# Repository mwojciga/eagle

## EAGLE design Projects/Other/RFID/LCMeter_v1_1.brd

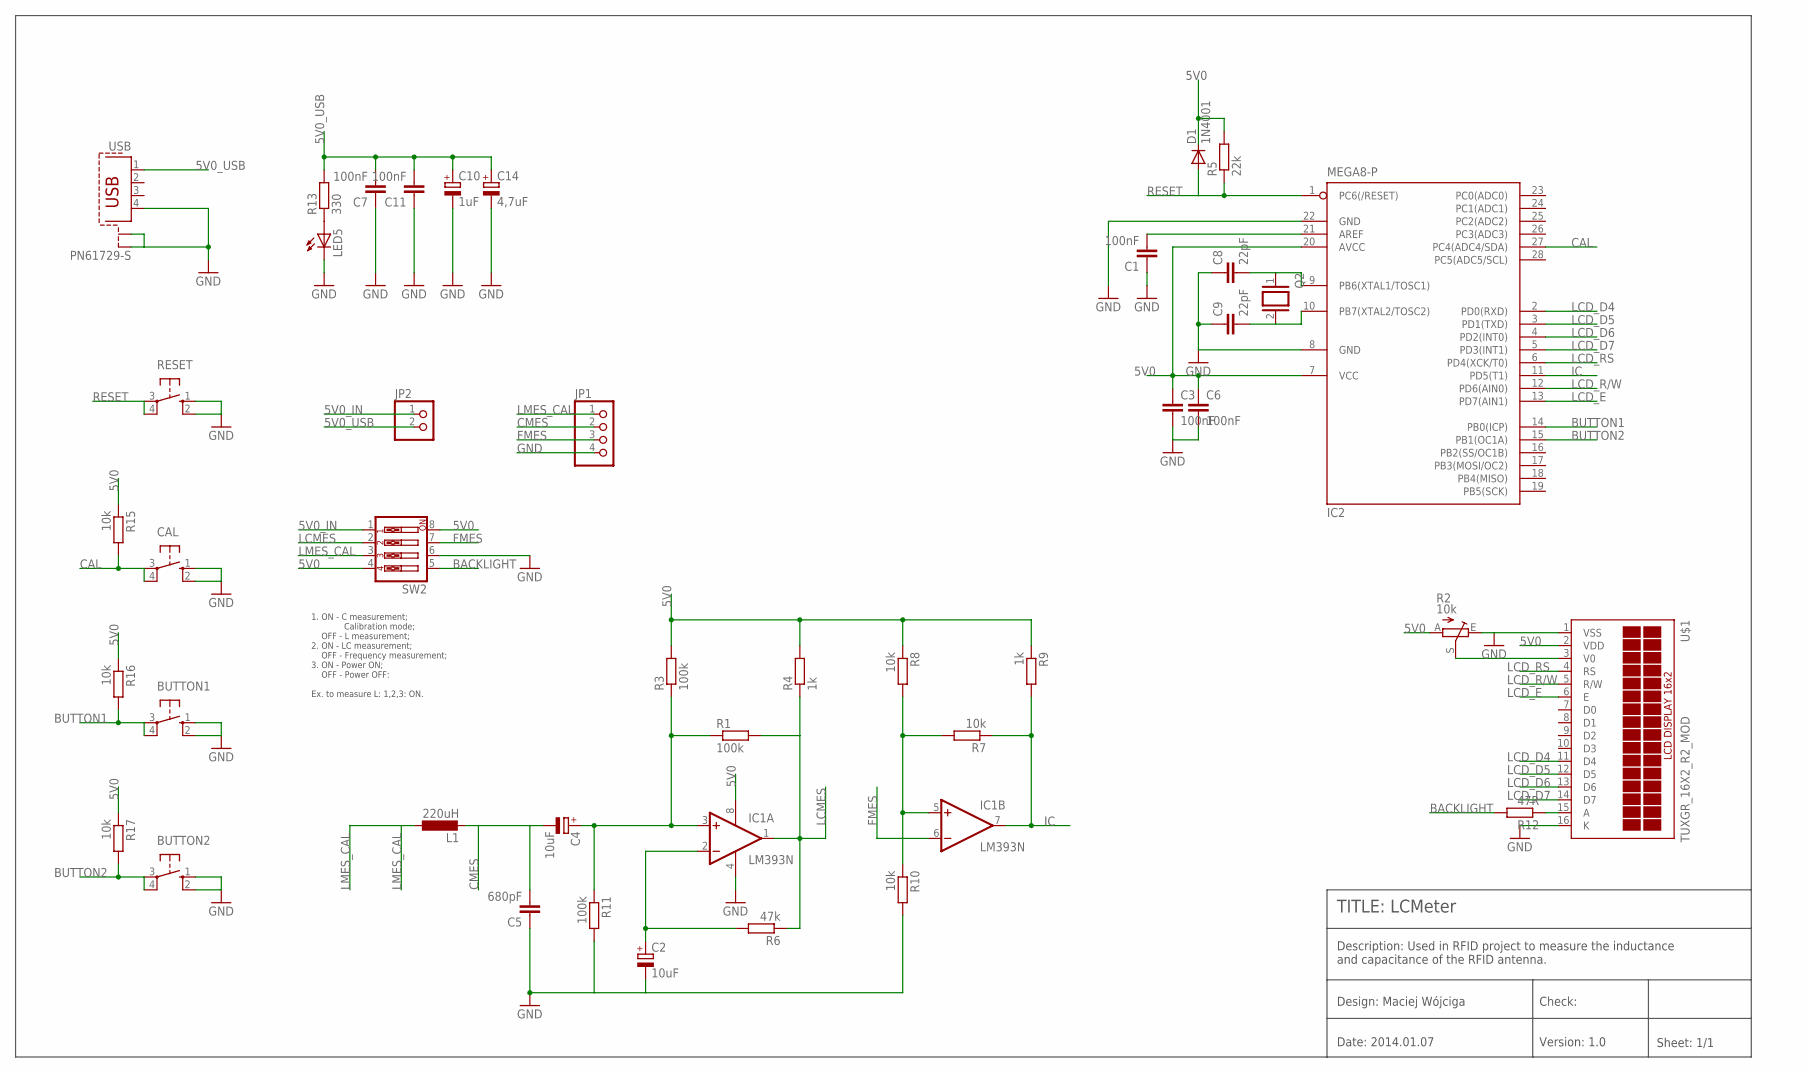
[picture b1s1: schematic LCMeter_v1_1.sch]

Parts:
BUTTON1, BUTTON2: 10-XX; B3F-10XX
C1, C3, C6, C7, C11: 100nF; C025-025X050
C2, C4: 10uF; E2,5-6E
C5: 680pF; C025-025X050
C8, C9: 22pF; C025-025X050
C10: 1uF; E2,5-5
C14: 4,7uF; E2,5-5
CAL: 10-XX; B3F-10XX
D1: 1N4001; DO41-10
IC1: LM393N; DIL08
IC2: MEGA8-P; DIL28-3
JP1: PINHD-1X4; 1X04
JP2: PINHD-1X2/90; 1X02/90
L1: 220uH; 6000-XXXX-RC
LED5: LED3MM
Q2: XTAL/S; QS
R1, R3, R11: 100k; 0207/10
R2: 10k; RJ9W
R4, R9: 1k; 0207/10
R5: 22k; 0207/10
R6: 47k; 0207/10
R7, R8, R10, R15, R16, R17: 10k; 0207/10
R12: 47R; 0207/10
R13: 330; 0207/10
RESET: 10-XX; B3F-10XX
SW2: SW_DIP-4; EDG-04
U$1: TUXGR_16X2_R2_MOD
USB: PN61729-S

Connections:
5V0: C3.1, C6.1, D1.C, IC1.8 (V+), IC2.7 (VCC), IC2.20 (AVCC), R2.A, R3.2, R4.2, R5.2, R8.1, R9.1, R15.1, R16.1, R17.1, SW2.4, SW2.8, U$1.2 (VDD)
5V0_IN: JP2.1, SW2.1
5V0_USB: C7.2, C10.+, C11.2, C14.+, JP2.2, R13.2, USB.1
BACKLIGHT: R12.2, SW2.5
BUTTON1: BUTTON1.3, BUTTON1.4 (P1), IC2.14 (PB0(ICP)), R16.2
BUTTON2: BUTTON2.3, BUTTON2.4 (P1), IC2.15 (PB1(OC1A)), R17.2
CAL: CAL.3, CAL.4 (P1), IC2.27 (PC4(ADC4/SDA)), R15.2
CMES: C4.-, C5.2, JP1.2, L1.2
FMES: IC1.6 (-IN), JP1.3, SW2.7
GND: BUTTON1.1 (S), BUTTON1.2 (S1), BUTTON2.1 (S), BUTTON2.2 (S1), C1.1, C2.-, C3.2, C5.1, C6.2, C7.1, C8.1, C9.1, C10.-, C11.1, C14.-, CAL.1 (S), CAL.2 (S1), IC1.4 (V-), IC2.8 (GND), IC2.22 (GND), JP1.4, LED5.K (C), R2.E, R10.2, R11.2, RESET.1 (S), RESET.2 (S1), SW2.6, U$1.1 (VSS), U$1.16 (K), USB.4, USB.S1, USB.S2
IC: IC1.7 (OUT), IC2.11 (PD5(T1)), R7.1, R9.2
LCD_D4: IC2.2 (PD0(RXD)), U$1.11 (D4)
LCD_D5: IC2.3 (PD1(TXD)), U$1.12 (D5)
LCD_D6: IC2.4 (PD2(INT0)), U$1.13 (D6)
LCD_D7: IC2.5 (PD3(INT1)), U$1.14 (D7)
LCD_E: IC2.13 (PD7(AIN1)), U$1.6 (E)
LCD_R/W: IC2.12 (PD6(AIN0)), U$1.5 (R/W)
LCD_RS: IC2.6 (PD4(XCK/T0)), U$1.4 (RS)
LCMES: IC1.1 (OUT), R1.2, R4.1, R6.1, SW2.2
LMES_CAL: JP1.1, L1.1, SW2.3
unnamed: C1.2, IC2.21 (AREF)
unnamed: C2.+, IC1.2 (-IN), R6.2
unnamed: R2.S, U$1.3 (V0)
unnamed: C4.+, IC1.3 (+IN), R1.1, R3.1, R11.1
unnamed: LED5.A, R13.1
unnamed: IC1.5 (+IN), R7.2, R8.2, R10.1
unnamed: R12.1, U$1.15 (A)
unnamed: C8.2, IC2.9 (PB6(XTAL1/TOSC1)), Q2.1
unnamed: C9.2, IC2.10 (PB7(XTAL2/TOSC2)), Q2.2
RESET: D1.A, IC2.1 (PC6(/RESET)), R5.1, RESET.3, RESET.4 (P1)

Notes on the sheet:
TITLE: LCMeter
Design: Maciej Wójciga
Check:
Date: 2014.01.07
Version: 1.0
Sheet: 1/1
Description: Used in RFID project to measure the inductance and capacitance of the RFID antenna.
1. ON - C measurement; Calibration mode; OFF - L measurement; 2. ON - LC measurement; OFF - Frequency measurement; 3. ON - Power ON; OFF - Power OFF: Ex. to measure L: 1,2,3: ON.

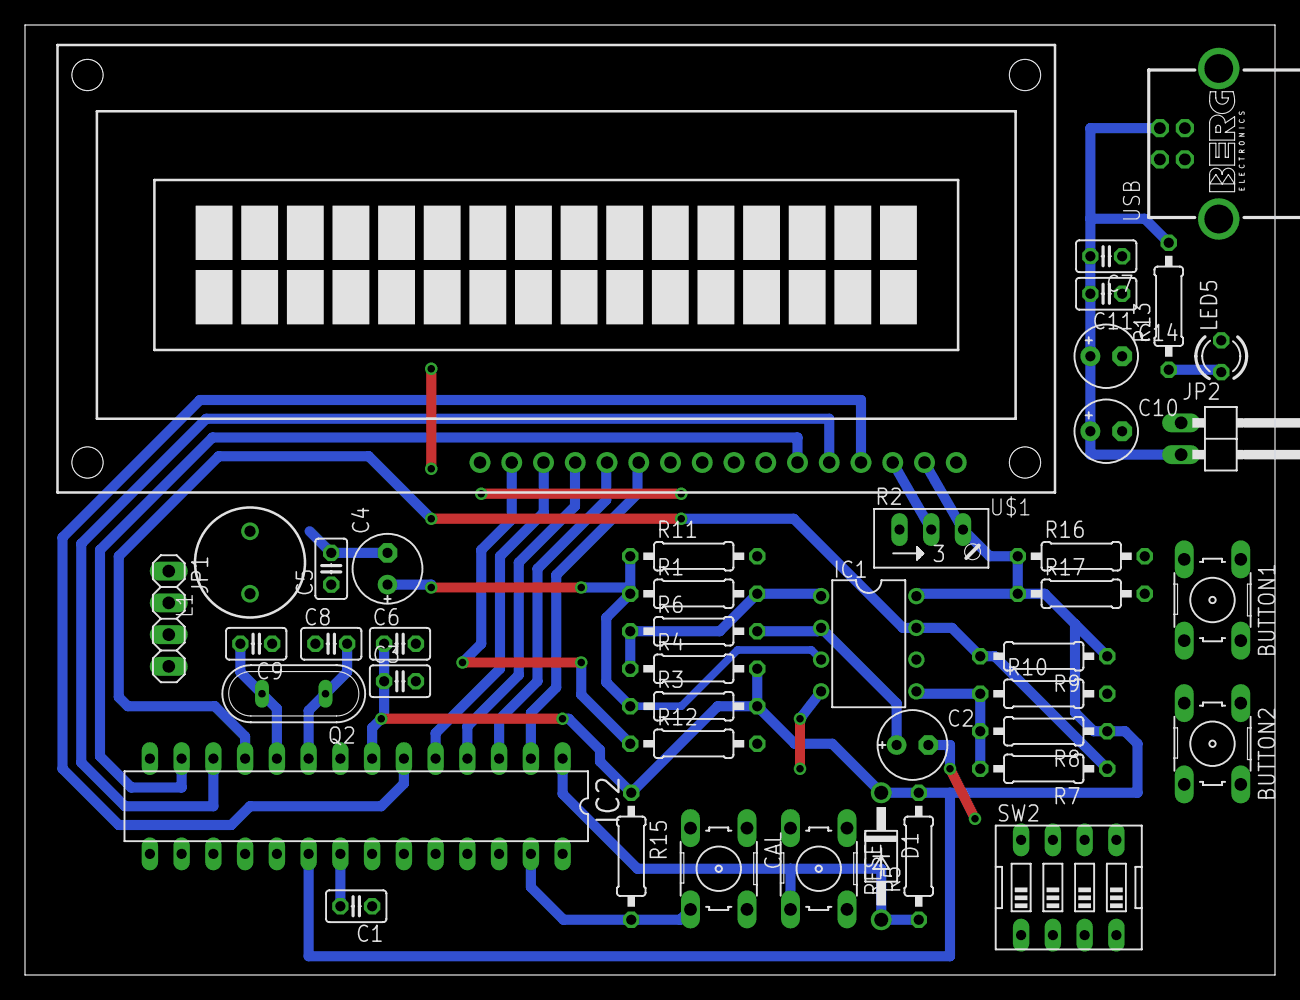
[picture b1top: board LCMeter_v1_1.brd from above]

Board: 2 copper layers, 100.0 x 76.0 mm, 43 parts (0 on the bottom side), 30 nets.

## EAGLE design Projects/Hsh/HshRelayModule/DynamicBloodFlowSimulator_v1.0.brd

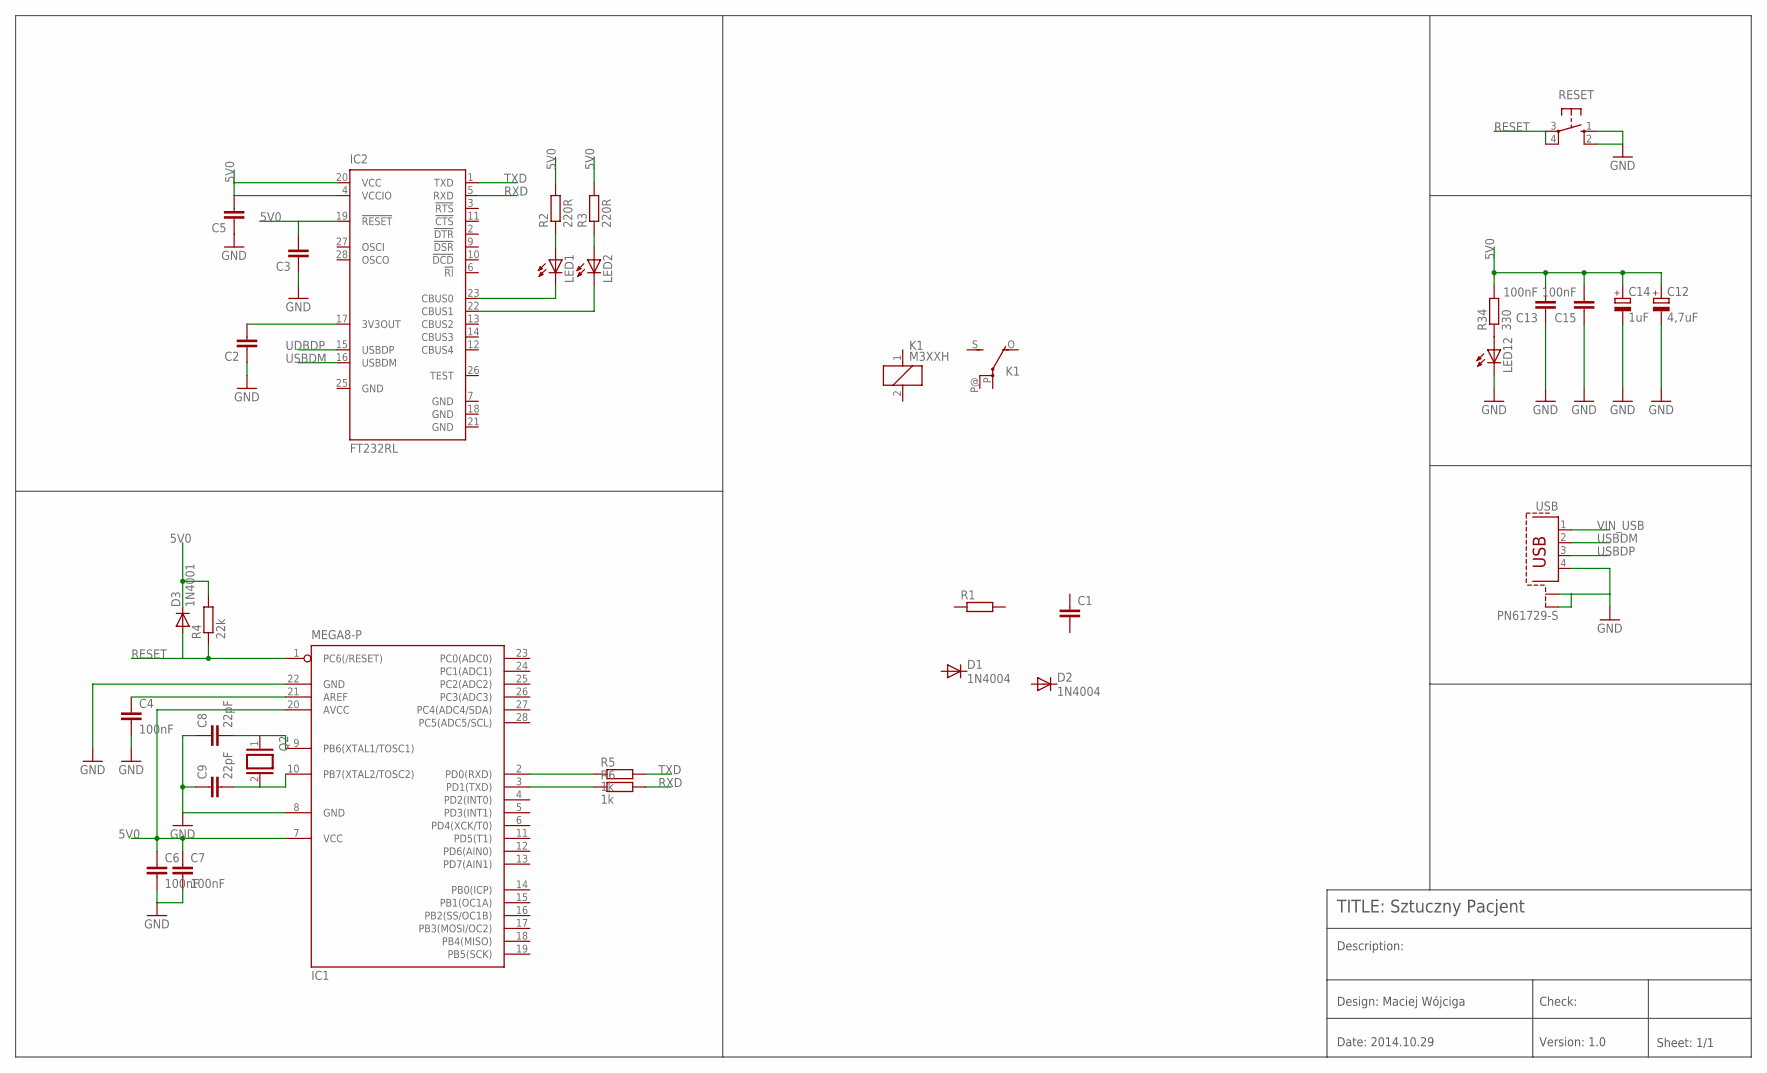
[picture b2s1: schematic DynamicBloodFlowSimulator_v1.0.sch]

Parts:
C1, C2, C3, C5: C-EU025-025X050; C025-025X050
C4: 100nF; C0805
C6, C7, C13, C15: 100nF; C025-025X050
C8, C9: 22pF; C025-025X050
C12: 4,7uF; E2,5-5
C14: 1uF; E2,5-5
D1, D2: 1N4004; DO41-10
D3: 1N4001; DO41-10
IC1: MEGA8-P; DIL28-3
IC2: FT232RL; SSOP28
K1: M3XXH
LED1, LED2, LED12: LED3MM
Q2: XTAL/S; QS
R1: R-EU_0207/10; 0207/10
R2, R3: 220R; 0207/10
R4: 22k; 0207/10
R5, R6: 1k; 0207/10
R34: 330; 0207/10
RESET: 10-XX; B3F-10XX
USB: PN61729-S

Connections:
5V0: C3.2, C5.2, C6.1, C7.1, C12.+, C13.2, C14.+, C15.2, D3.C, IC1.7 (VCC), IC1.20 (AVCC), IC2.4 (VCCIO), IC2.19 (!RESET), IC2.20 (VCC), R2.2, R3.2, R4.2, R34.2
GND: C2.1, C3.1, C4.2, C5.1, C6.2, C7.2, C8.1, C9.1, C12.-, C13.1, C14.-, C15.1, IC1.8 (GND), IC1.22 (GND), IC2.7 (GND), IC2.18 (GND), IC2.21 (GND), IC2.25 (GND), LED12.K (C), RESET.1 (S), RESET.2 (S1), USB.4, USB.S1, USB.S2
unnamed: C2.2, IC2.17 (3V3OUT)
unnamed: LED1.A, R2.1
unnamed: IC2.23 (CBUS0), LED1.K (C)
unnamed: IC2.22 (CBUS1), LED2.K (C)
unnamed: LED2.A, R3.1
unnamed: C4.1, IC1.21 (AREF)
unnamed: IC1.2 (PD0(RXD)), R5.1
unnamed: IC1.3 (PD1(TXD)), R6.1
unnamed: C8.2, IC1.9 (PB6(XTAL1/TOSC1)), Q2.1
unnamed: C9.2, IC1.10 (PB7(XTAL2/TOSC2)), Q2.2
unnamed: LED12.A, R34.1
RESET: D3.A, IC1.1 (PC6(/RESET)), R4.1, RESET.3, RESET.4 (P1)
RXD: IC2.5 (RXD), R6.2
TXD: IC2.1 (TXD), R5.2
UDBDP: IC2.15 (USBDP)
USBDM: IC2.16 (USBDM), USB.2
USBDP: USB.3
VIN_USB: USB.1

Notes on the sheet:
TITLE: Sztuczny Pacjent
Design: Maciej Wójciga
Check:
Date: 2014.10.29
Version: 1.0
Sheet: 1/1
Description:

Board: 2 copper layers, 32 parts (0 on the bottom side), 17 nets, no tracks yet.

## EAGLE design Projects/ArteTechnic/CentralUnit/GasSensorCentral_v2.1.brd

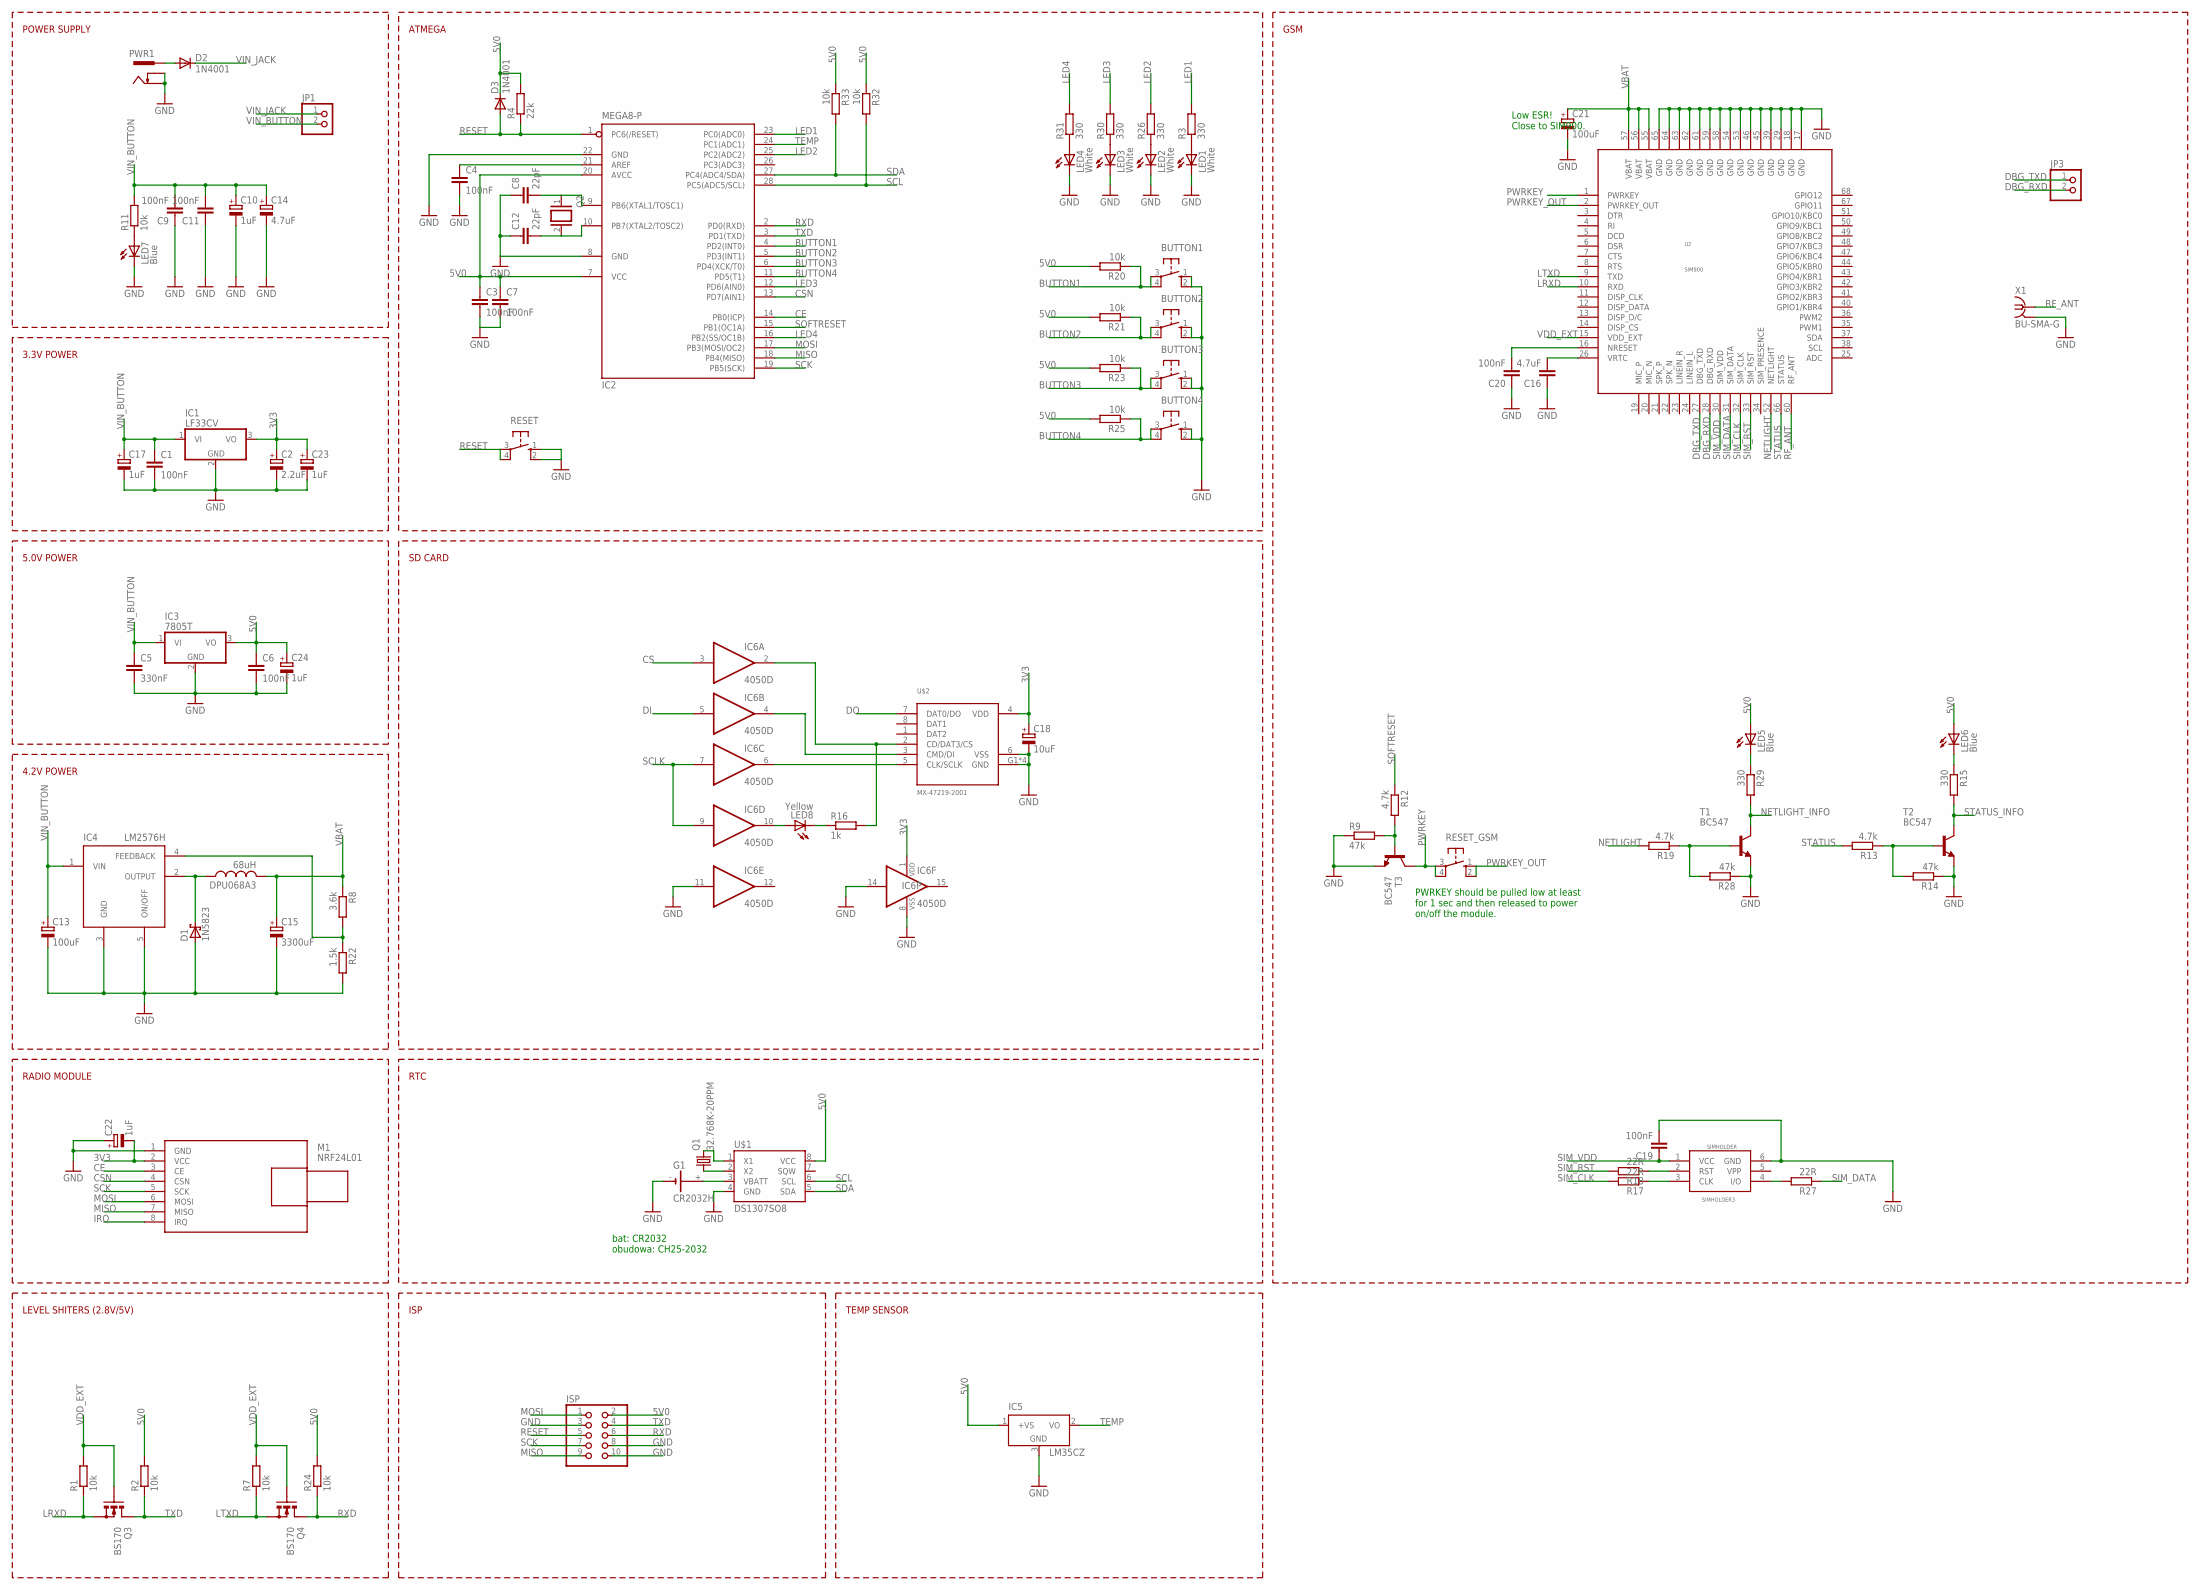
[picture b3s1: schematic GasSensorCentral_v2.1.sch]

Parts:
BUTTON1, BUTTON2, BUTTON3, BUTTON4: 10-XX; B3F-10XX
C1, C3, C4, C6, C7, C9, C11, C19, C20: 100nF; C025-025X050
C2: 2.2uF; E2,5-5
C5: 330nF; C025-025X050
C8, C12: 22pF; C025-025X050
C10, C17, C22, C23, C24: 1uF; E2,5-5
C13, C21: 100uF; E2,5-5
C14: 4.7uF; E2,5-5
C15: 3300uF; E5-13
C16: 4.7uF; C025-025X050
C18: 10uF; E2,5-5
D1: 1N5823; DO41-7.6
D2, D3: 1N4001; DO41-10
DPU068A3: 68uH; TJ4-U1
G1: CR2032H
IC1: LF33CV; TO220H
IC2: MEGA8-P; DIL28-3
IC3: 7805T; TO220H
IC4: LM2576H; TO220-52
IC5: LM35CZ; TO92
IC6: 4050D; SO16
ISP: PINHD-2X5; 2X05
JP1, JP3: PINHD-1X2; 1X02
LED1, LED2, LED3, LED4: White; LED3MM
LED5, LED6, LED7: Blue; LED3MM
LED8: Yellow; LED3MM
M1: NRF24L01; WIRELESS-NRD24L01-PA-EXT
PWR1: PWR-JAKPWR_JACK_UNI_MILLING; PWR_JACK_UNI_MILLING
Q1: 32.768K-20PPM; TC26V
Q2: XTAL/S; QS
Q3, Q4: BS170; SOT54E
R1, R2, R7, R11, R20, R21, R23, R24, R25, R32, R33: 10k; 0207/10
R3, R15, R26, R29, R30, R31: 330; 0207/10
R4: 22k; 0207/10
R8: 3.6k; 0207/10
R9, R14, R28: 47k; 0207/10
R12, R13, R19: 4.7k; 0207/10
R16: 1k; 0207/10
R17, R18, R27: 22R; 0207/10
R22: 1.5k; 0207/10
RESET: 10-XX; B3F-10XX
RESET_GSM: 10-XX; B3F-10XX
SIMHOLDER: SIMHOLDER3
T1, T2, T3: BC547; TO92
U2: SIM900
U$1: DS1307SO8; SO08
U$2: MX-47219-2001
X1: BU-SMA-G

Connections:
3V3: C2.+, C18.+, C22.-, C23.+, IC1.3 (VO), IC6.1 (VDD), M1.2 (VCC), U$2.4 (VDD)
5V0: C3.1, C6.1, C7.1, C24.+, D3.C, IC2.7 (VCC), IC2.20 (AVCC), IC3.3 (VO), IC5.1 (+VS), ISP.2, LED5.A, LED6.A, R2.2, R4.2, R20.2, R21.2, R23.2, R24.2, R25.2, R32.1, R33.1, U$1.8 (VCC)
BUTTON1: BUTTON1.3, BUTTON1.4 (P1), IC2.4 (PD2(INT0)), R20.1
BUTTON2: BUTTON2.3, BUTTON2.4 (P1), IC2.5 (PD3(INT1)), R21.1
BUTTON3: BUTTON3.3, BUTTON3.4 (P1), IC2.6 (PD4(XCK/T0)), R23.1
BUTTON4: BUTTON4.3, BUTTON4.4 (P1), IC2.11 (PD5(T1)), R25.1
CE: IC2.14 (PB0(ICP)), M1.3 (CE)
CS: IC6.3 (I)
CSN: IC2.13 (PD7(AIN1)), M1.4 (CSN)
DBG_RXD: JP3.2, U2.28 (DBG_RXD)
DBG_TXD: JP3.1, U2.27 (DBG_TXD)
DI: IC6.5 (I)
DO: U$2.7 (DAT0/DO)
GND: BUTTON1.1 (S), BUTTON1.2 (S1), BUTTON2.1 (S), BUTTON2.2 (S1), BUTTON3.1 (S), BUTTON3.2 (S1), BUTTON4.1 (S), BUTTON4.2 (S1), C1.2, C2.-, C3.2, C4.2, C5.2, C6.2, C7.2, C8.1, C9.1, C10.-, C11.1, C12.1, C13.-, C14.-, C15.-, C16.1, C17.-, C18.-, C19.2, C20.1, C21.-, C22.+, C23.-, C24.-, D1.A, G1.-, IC1.2 (GND), IC2.8 (GND), IC2.22 (GND), IC3.2 (GND), IC4.3 (GND), IC4.5 (ON/OFF), IC5.3 (GND), IC6.8 (VSS), IC6.11 (I), IC6.14 (I), ISP.3, ISP.8, ISP.10, LED1.K (C), LED2.K (C), LED3.K (C), LED4.K (C), LED7.K (C), M1.1 (GND), PWR1.-, PWR1.--, R9.1, R14.1, R22.2, R28.1, RESET.1 (S), RESET.2 (S1), SIMHOLDER.6 (GND), T1.1 (E), T2.1 (E), T3.1 (E), U2.17 (GND), U2.18 (GND), U2.29 (GND), U2.39 (GND), U2.45 (GND), U2.46 (GND), U2.53 (GND), U2.54 (GND), U2.58 (GND), U2.59 (GND), U2.61 (GND), U2.62 (GND), U2.63 (GND), U2.64 (GND), U2.65 (GND), U$1.4 (GND), U$2.6 (VSS), U$2.G1 (GND), U$2.G2 (GND), U$2.G3 (GND), U$2.G4 (GND), X1.2, X1.3 (2), X1.4 (2), X1.5 (2)
IRQ: M1.8 (IRQ)
LED1: IC2.23 (PC0(ADC0)), R3.2
LED2: IC2.25 (PC2(ADC2)), R26.2
LED3: IC2.12 (PD6(AIN0)), R30.2
LED4: IC2.16 (PB2(SS/OC1B)), R31.2
LRXD: Q3.S, R1.1, U2.10 (RXD)
LTXD: Q4.S, R7.1, U2.9 (TXD)
MISO: IC2.18 (PB4(MISO)), ISP.9, M1.7 (MISO)
MOSI: IC2.17 (PB3(MOSI/OC2)), ISP.1, M1.6 (MOSI)
unnamed: C4.1, IC2.21 (AREF)
unnamed: Q1.1, U$1.2 (X2)
unnamed: IC4.4 (FEEDBACK), R8.2, R22.1
unnamed: D2.A, PWR1.+
unnamed: LED1.A, R3.1
unnamed: R27.2, SIMHOLDER.4 (I/O)
unnamed: LED5.K (C), R29.1
unnamed: Q1.2, U$1.1 (X1)
unnamed: R13.1, R14.2, T2.2 (B)
unnamed: LED7.A, R11.1
unnamed: LED6.K (C), R15.1
unnamed: D1.C, DPU068A3.1, IC4.2 (OUTPUT)
unnamed: C20.2, U2.16 (NRESET)
unnamed: R9.2, R12.2, T3.2 (B)
unnamed: R19.1, R28.2, T1.2 (B)
unnamed: G1.+, U$1.3 (VBATT)
unnamed: C16.2, U2.26 (VRTC)
unnamed: LED2.A, R26.1
unnamed: LED3.A, R30.1
unnamed: LED4.A, R31.1
unnamed: R18.1, SIMHOLDER.2 (RST)
unnamed: R17.1, SIMHOLDER.3 (CLK)
unnamed: IC6.2 (O), R16.2, U$2.2 (CD/DAT3/CS)
unnamed: IC6.4 (O), U$2.3 (CMD/DI)
unnamed: C8.2, IC2.9 (PB6(XTAL1/TOSC1)), Q2.1
unnamed: IC6.6 (O), U$2.5 (CLK/SCLK)
unnamed: IC6.10 (O), LED8.A
unnamed: LED8.K (C), R16.1
unnamed: C12.2, IC2.10 (PB7(XTAL2/TOSC2)), Q2.2
NETLIGHT: R19.2, U2.52 (NETLIGHT)
NETLIGHT_INFO: R29.2, T1.3 (C)
PWRKEY: RESET_GSM.3, RESET_GSM.4 (P1), T3.3 (C), U2.1 (PWRKEY)
PWRKEY_OUT: RESET_GSM.1 (S), RESET_GSM.2 (S1), U2.2 (PWRKEY_OUT)
RESET: D3.A, IC2.1 (PC6(/RESET)), ISP.5, R4.1, RESET.3, RESET.4 (P1)
RF_ANT: U2.60 (RF_ANT), X1.1
RXD: IC2.2 (PD0(RXD)), ISP.6, Q4.D, R24.1
SCK: IC2.19 (PB5(SCK)), ISP.7, M1.5 (SCK)
SCL: IC2.28 (PC5(ADC5/SCL)), R32.2, U$1.6 (SCL)
SCLK: IC6.7 (I), IC6.9 (I)
SDA: IC2.27 (PC4(ADC4/SDA)), R33.2, U$1.5 (SDA)
SIM_CLK: R17.2, U2.32 (SIM_CLK)
SIM_DATA: R27.1, U2.31 (SIM_DATA)
SIM_RST: R18.2, U2.33 (SIM_RST)
SIM_VDD: C19.1, SIMHOLDER.1 (VCC), U2.30 (SIM_VDD)
SOFTRESET: IC2.15 (PB1(OC1A)), R12.1
STATUS: R13.2, U2.66 (STATUS)
STATUS_INFO: R15.2, T2.3 (C)
TEMP: IC2.24 (PC1(ADC1)), IC5.2 (VO)
TXD: IC2.3 (PD1(TXD)), ISP.4, Q3.D, R2.1
VBAT: C15.+, C21.+, DPU068A3.2, R8.1, U2.55 (VBAT), U2.56 (VBAT), U2.57 (VBAT)
VDD_EXT: Q3.G, Q4.G, R1.2, R7.2, U2.15 (VDD_EXT)
VIN_BUTTON: C1.1, C5.1, C9.2, C10.+, C11.2, C13.+, C14.+, C17.+, IC1.1 (VI), IC3.1 (VI), IC4.1 (VIN), JP1.2, R11.2
VIN_JACK: D2.C, JP1.1

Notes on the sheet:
PWRKEY should be pulled low at least for 1 sec and then released to power on/off the module.
Low ESR! Close to SIM900.
bat: CR2032 obudowa: CH25-2032
POWER SUPPLY
3.3V POWER
5.0V POWER
4.2V POWER
RADIO MODULE
LEVEL SHITERS (2.8V/5V)
ATMEGA
SD CARD
RTC
ISP
GSM
TEMP SENSOR

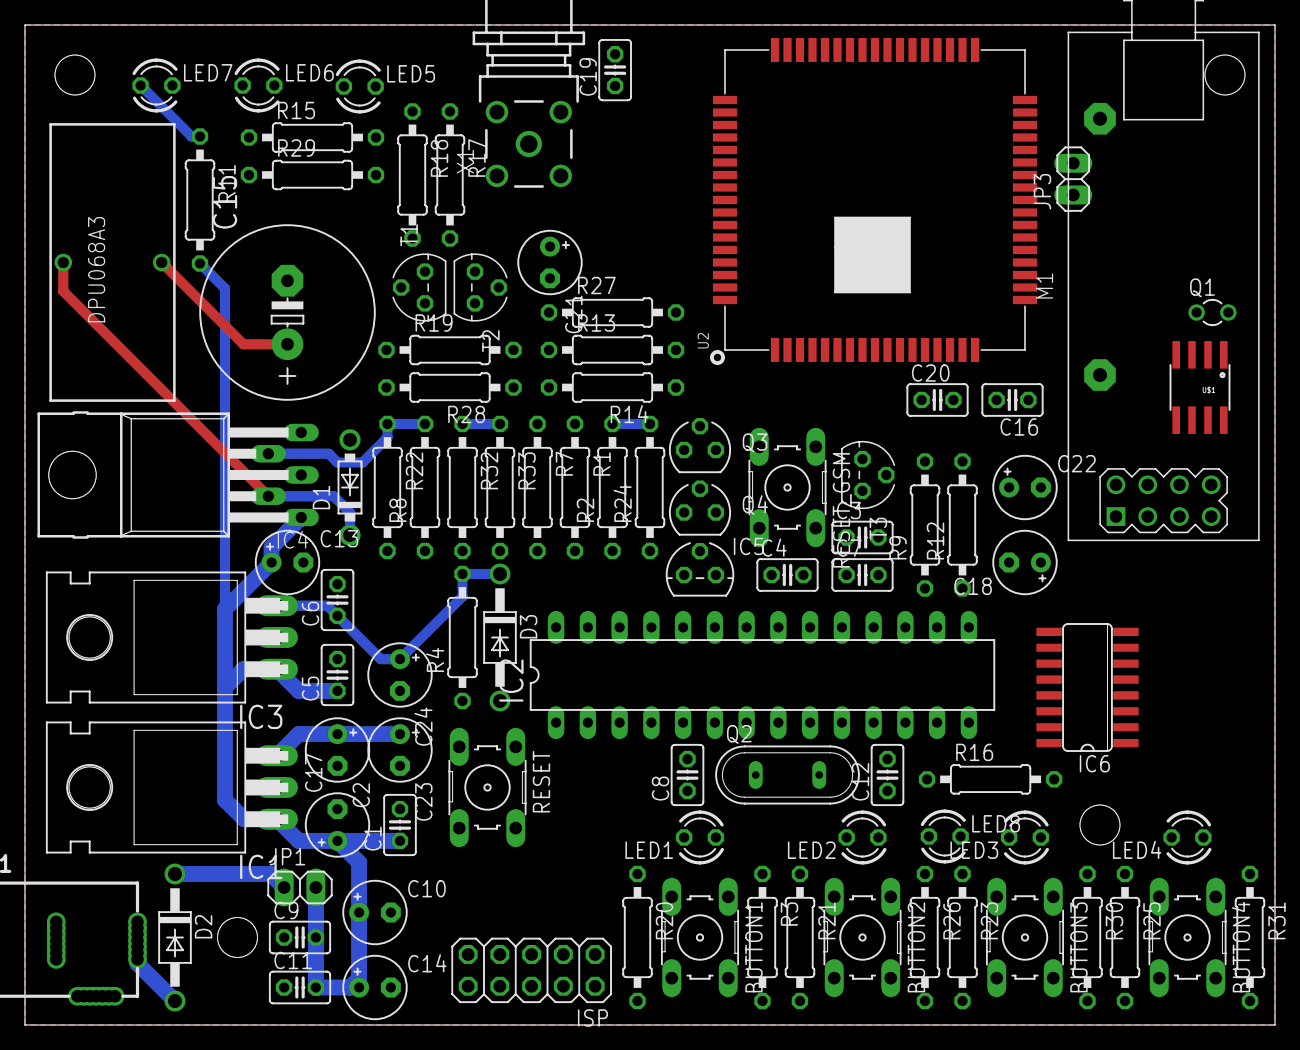
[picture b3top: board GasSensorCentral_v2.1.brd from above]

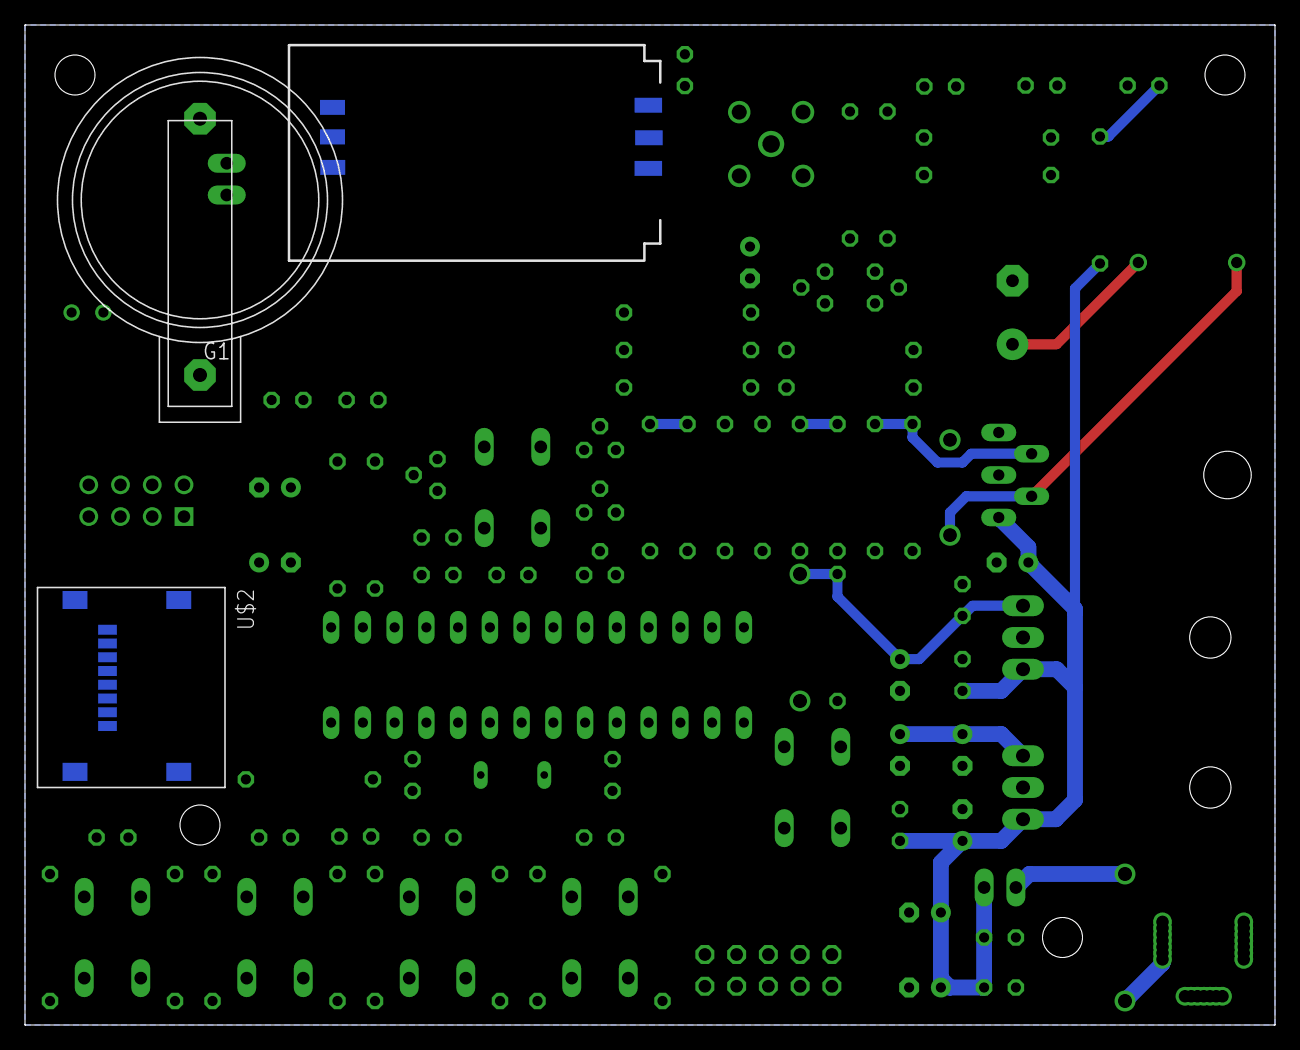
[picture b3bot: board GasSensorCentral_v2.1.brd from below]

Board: 2 copper layers, 100.0 x 80.0 mm, 96 parts (3 on the bottom side), 72 nets.

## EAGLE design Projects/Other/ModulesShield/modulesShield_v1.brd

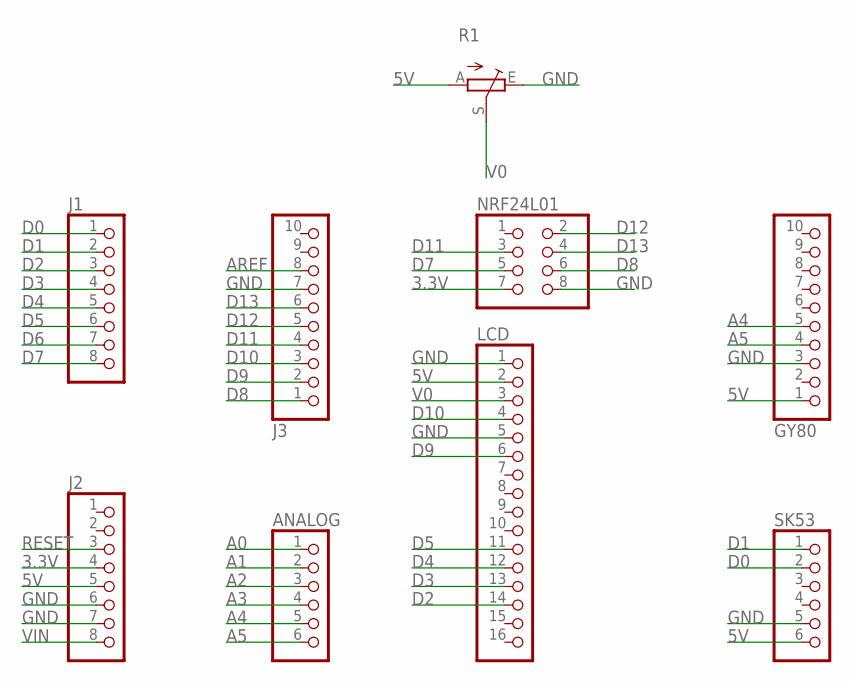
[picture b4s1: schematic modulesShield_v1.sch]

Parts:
ANALOG: PINHD-1X6; 1X06
GY80: PINHD-1X10TH; 1X10-TH
J1, J2: PINHD-1X8TH; 1X08-TH
J3: PINHD-1X10TH; 1X10-TH
LCD: PINHD-1X16; 1X16
NRF24L01: PINHD-2X4; 2X04
R1: TRIM_EU-CA6V; CA6V
SK53: PINHD-1X6; 1X06

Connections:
3.3V: J2.4, NRF24L01.7
5V: GY80.1, J2.5, LCD.2, R1.A, SK53.6
A0: ANALOG.1
A1: ANALOG.2
A2: ANALOG.3
A3: ANALOG.4
A4: ANALOG.5, GY80.5
A5: ANALOG.6, GY80.4
AREF: J3.8
D0: J1.1, SK53.2
D1: J1.2, SK53.1
D2: J1.3, LCD.14
D3: J1.4, LCD.13
D4: J1.5, LCD.12
D5: J1.6, LCD.11
D6: J1.7
D7: J1.8, NRF24L01.5
D8: J3.1, NRF24L01.6
D9: J3.2, LCD.6
D10: J3.3, LCD.4
D11: J3.4, NRF24L01.3
D12: J3.5, NRF24L01.2
D13: J3.6, NRF24L01.4
GND: GY80.3, J2.6, J2.7, J3.7, LCD.1, LCD.5, NRF24L01.8, R1.E, SK53.5
RESET: J2.3
V0: LCD.3, R1.S
VIN: J2.8

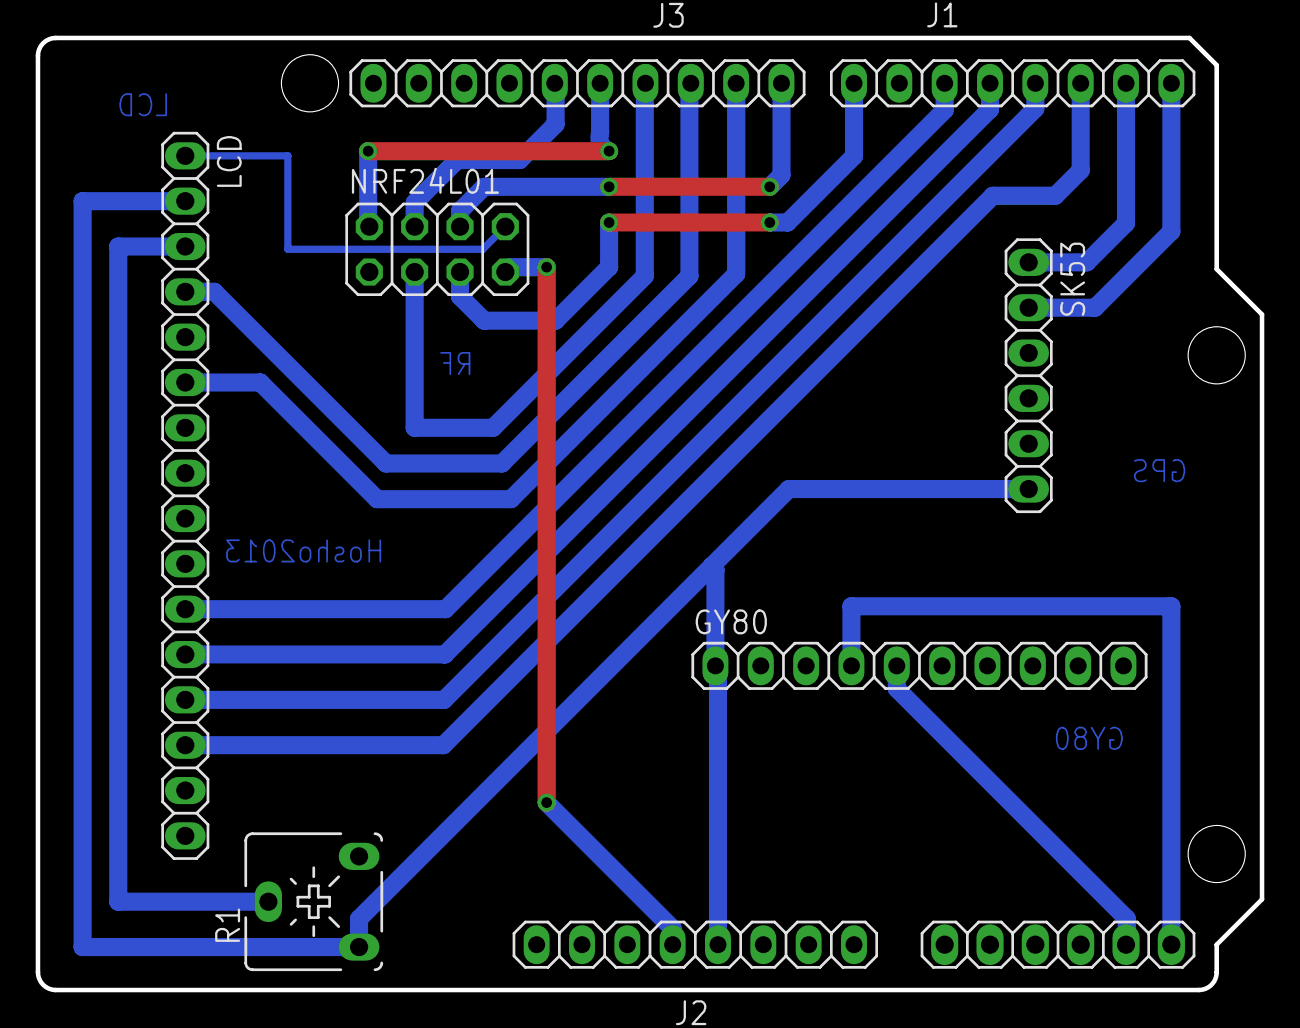
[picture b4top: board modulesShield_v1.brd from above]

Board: 2 copper layers, 68.6 x 53.3 mm, 9 parts (0 on the bottom side), 19 nets.

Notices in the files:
parts and their libraries:
diy-modules: Released under the Creative Commons Attribution 4.0 International License: http://creativecommons.org/licenses/by/4.0
SparkFun-FreqCtrl: Licensing: Creative Commons ShareAlike 4.0 International - https://creativecommons.org/licenses/by-sa/4.0
